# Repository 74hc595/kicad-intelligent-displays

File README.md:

# Intelligent Display Symbols/Footprints for KiCad

KiCad symbols and footprints for 4- and 8-character intelligent segmented/dot-matrix alphanumeric displays like the DL1414, DL2416, HDSP-2112, PDSP1881, etc.

At this time, the library does not include symbols/footprints for the exotic/mil-spec parts.

Some parts, like the PDSP188x and HDSP-2xxx, do not have pins in all positions. To facilitate the use of regular DIP sockets and single inline pin sockets, alternative footprints have been provided for these parts that have holes in all positions. (they end with a `_DIPxx` suffix)

(Pictures courtesy of the [Vintage Technology Association](http://www.decadecounter.com/))

## Test fixture

Included in the KiCad project is a tester board based on the atmega809 microcontroller. The `code` folder contains the firmware, and instructions are in `code/main.c`. A prebuilt hex file is also provided.

## References

[1982 Litronix Optoelectronics Catalog](https://archive.org/details/LitronixOptoelectronicsCatalog1982)

[1985 Siemens Optoelectronics Catalog](http://www.bitsavers.org/components/siemens/1985_Siemens_Optoelectronics_Catalog.pdf)

[1990 Siemens Optoelectronics Data Book](http://www.bitsavers.org/components/siemens/1990_Siemens_Optoelectronics_Data_Book.pdf)

[Broadcom Smart Alphanumeric Displays](https://www.broadcom.com/products/leds-and-displays/smart-alphanumeric-displays/parallel-interface/)

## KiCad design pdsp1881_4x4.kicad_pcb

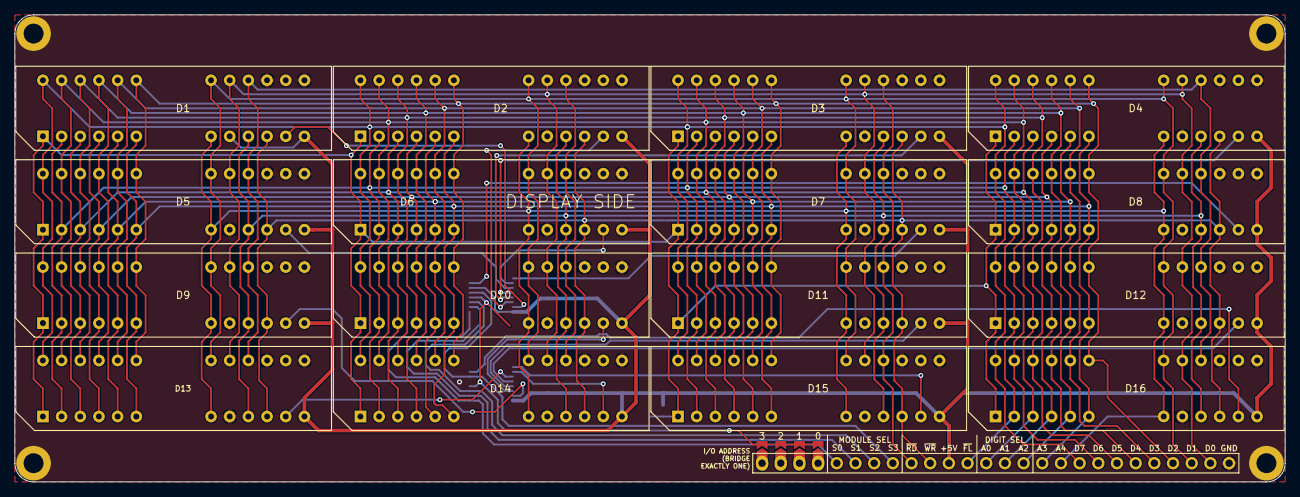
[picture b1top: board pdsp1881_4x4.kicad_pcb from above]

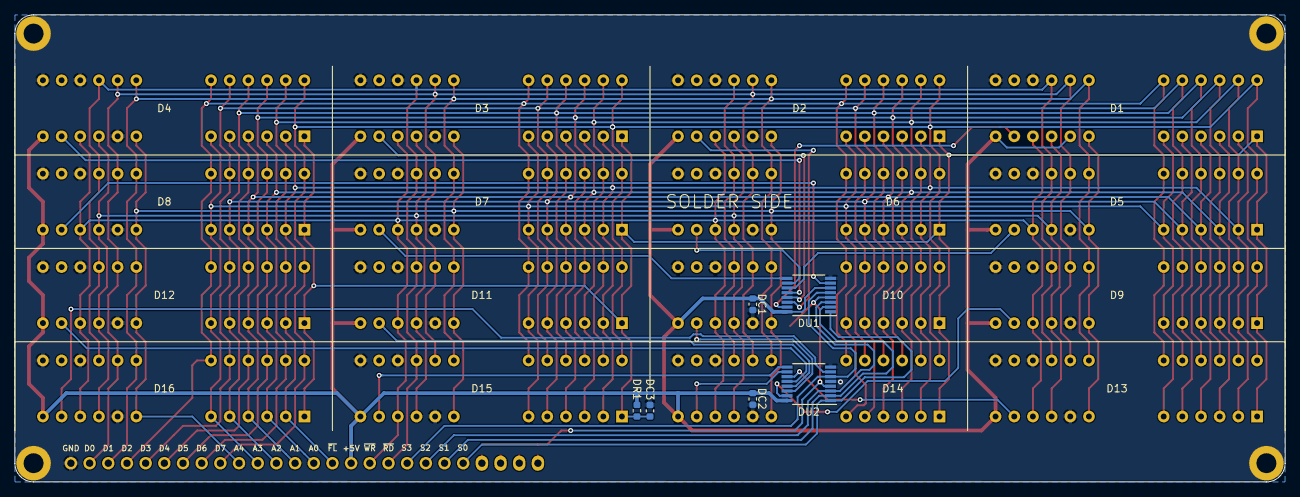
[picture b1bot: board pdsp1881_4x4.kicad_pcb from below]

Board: 2 copper layers, 172.7 x 63.5 mm, 27 parts (6 on the bottom side), 45 nets.

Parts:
D1, D2, D3, D4, D5, D6, D7, D8, D9, D10, D11, D12, D13, D14, D15, D16: PDSP1881; PDSP188x
DC1, DC2, DC3: 0.1uF; C_0603_1608Metric
DJ1: Conn_01x26; PinHeader_1x26_P2.54mm_Vertical
DJP1, DJP2, DJP3, DJP4: SolderJumper_2_Open; SolderJumper-2_P1.3mm_Open_TrianglePad1.0x1.5mm
DR1: 10k; R_0603_1608Metric
DU1, DU2: 74AHC138; TSSOP-16_4.4x5mm_P0.65mm

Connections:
/A0: D1.3, D2.3, D3.3, D4.3, D5.3, D6.3, D7.3, D8.3, D9.3, D10.3, D11.3, D12.3, D13.3, D14.3, D15.3, D16.3, DJ1.13
/A1: D1.4, D2.4, D3.4, D4.4, D5.4, D6.4, D7.4, D8.4, D9.4, D10.4, D11.4, D12.4, D13.4, D14.4, D15.4, D16.4, DJ1.14
/A2: D1.5, D2.5, D3.5, D4.5, D5.5, D6.5, D7.5, D8.5, D9.5, D10.5, D11.5, D12.5, D13.5, D14.5, D15.5, D16.5, DJ1.15
/A3: D1.6, D2.6, D3.6, D4.6, D5.6, D6.6, D7.6, D8.6, D9.6, D10.6, D11.6, D12.6, D13.6, D14.6, D15.6, D16.6, DJ1.16
/A4: D1.10, D2.10, D3.10, D4.10, D5.10, D6.10, D7.10, D8.10, D9.10, D10.10, D11.10, D12.10, D13.10, D14.10, D15.10, D16.10, DJ1.17
/D0: D1.20, D2.20, D3.20, D4.20, D5.20, D6.20, D7.20, D8.20, D9.20, D10.20, D11.20, D12.20, D13.20, D14.20, D15.20, D16.20, DJ1.25
/D1: D1.21, D2.21, D3.21, D4.21, D5.21, D6.21, D7.21, D8.21, D9.21, D10.21, D11.21, D12.21, D13.21, D14.21, D15.21, D16.21, DJ1.24
/D2: D1.25, D2.25, D3.25, D4.25, D5.25, D6.25, D7.25, D8.25, D9.25, D10.25, D11.25, D12.25, D13.25, D14.25, D15.25, D16.25, DJ1.23
/D3: D1.26, D2.26, D3.26, D4.26, D5.26, D6.26, D7.26, D8.26, D9.26, D10.26, D11.26, D12.26, D13.26, D14.26, D15.26, D16.26, DJ1.22
/D4: D1.27, D2.27, D3.27, D4.27, D5.27, D6.27, D7.27, D8.27, D9.27, D10.27, D11.27, D12.27, D13.27, D14.27, D15.27, D16.27, DJ1.21
/D5: D1.28, D2.28, D3.28, D4.28, D5.28, D6.28, D7.28, D8.28, D9.28, D10.28, D11.28, D12.28, D13.28, D14.28, D15.28, D16.28, DJ1.20
/D6: D1.29, D2.29, D3.29, D4.29, D5.29, D6.29, D7.29, D8.29, D9.29, D10.29, D11.29, D12.29, D13.29, D14.29, D15.29, D16.29, DJ1.19
/D7: D1.30, D2.30, D3.30, D4.30, D5.30, D6.30, D7.30, D8.30, D9.30, D10.30, D11.30, D12.30, D13.30, D14.30, D15.30, D16.30, DJ1.18
/DCLK: D1.12, D2.12, D3.12, D4.12, D5.12, D6.12, D7.12, D8.12, D9.12, D10.12, D11.12, D12.12, D13.12, D14.12, D15.12, D16.12
/S0: DJ1.5, DU1.1, DU2.1
/S1: DJ1.6, DU1.2, DU2.2
/S2: DJ1.7, DU1.3, DU2.3
/S3: DJ1.8, DU1.5, DU2.6
/~D1EN: D1.14, DU1.15
/~D2EN: D2.14, DU1.14
/~D3EN: D3.14, DU1.13
/~D4EN: D4.14, DU1.12
/~D5EN: D5.14, DU1.11
/~D6EN: D6.14, DU1.10
/~D7EN: D7.14, DU1.9
/~D8EN: D8.14, DU1.7
/~D9EN: D9.14, DU2.15
/~D10EN: D10.14, DU2.14
/~D11EN: D11.14, DU2.13
/~D12EN: D12.14, DU2.12
/~D13EN: D13.14, DU2.11
/~D14EN: D14.14, DU2.10
/~D15EN: D15.14, DU2.9
/~D16EN: D16.14, DU2.7
/~DISPEN: DJP1.2, DJP2.2, DJP3.2, DJP4.2, DU1.4, DU2.4
/~DRST: D1.1, D2.1, D3.1, D4.1, D5.1, D6.1, D7.1, D8.1, D9.1, D10.1, D11.1, D12.1, D13.1, D14.1, D15.1, D16.1, DC3.1, DR1.2
/~FL: D1.2, D2.2, D3.2, D4.2, D5.2, D6.2, D7.2, D8.2, D9.2, D10.2, D11.2, D12.2, D13.2, D14.2, D15.2, D16.2, DJ1.12
/~RD: D1.19, D2.19, D3.19, D4.19, D5.19, D6.19, D7.19, D8.19, D9.19, D10.19, D11.19, D12.19, D13.19, D14.19, D15.19, D16.19, DJ1.9
/~WR: D1.13, D2.13, D3.13, D4.13, D5.13, D6.13, D7.13, D8.13, D9.13, D10.13, D11.13, D12.13, D13.13, D14.13, D15.13, D16.13, DJ1.10
GND: D1.16, D1.18, D2.11, D2.16, D2.18, D3.11, D3.16, D3.18, D4.11, D4.16, D4.18, D5.11, D5.16, D5.18, D6.11, D6.16, D6.18, D7.11, D7.16, D7.18, D8.11, D8.16, D8.18, D9.11, D9.16, D9.18, D10.11, D10.16, D10.18, D11.11, D11.16, D11.18, D12.11, D12.16, D12.18, D13.11, D13.16, D13.18, D14.11, D14.16, D14.18, D15.11, D15.16, D15.18, D16.11, D16.16, D16.18, DC1.2, DC2.2, DC3.2, DJ1.26, DU1.8, DU2.5, DU2.8
unnamed: DJ1.1, DJP1.1
unnamed: DJ1.2, DJP2.1
unnamed: DJ1.3, DJP3.1
unnamed: DJ1.4, DJP4.1
VCC: D1.11, D1.15, D2.15, D3.15, D4.15, D5.15, D6.15, D7.15, D8.15, D9.15, D10.15, D11.15, D12.15, D13.15, D14.15, D15.15, D16.15, DC1.1, DC2.1, DJ1.11, DR1.1, DU1.6, DU1.16, DU2.16

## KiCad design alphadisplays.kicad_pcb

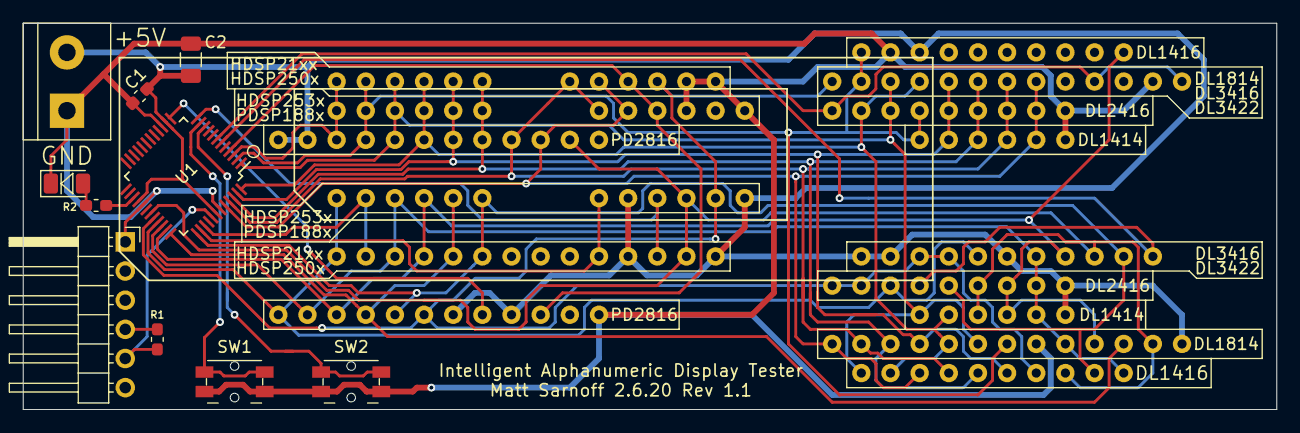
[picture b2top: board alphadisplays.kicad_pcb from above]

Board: 2 copper layers, 109.2 x 33.7 mm, 18 parts (0 on the bottom side), 30 nets.

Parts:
C1: 0.1uF; C_0603_1608Metric_Pad1.05x0.95mm_HandSolder
C2: 10uF; C_1206_3216Metric
D1: DL1414
D2: DL1416
D3: DL2416
D4: DL3416; DL34xx
D5: DL1814
D6: HDSP-250x
D7: PDSP188x
D8: PD2816
D9: 1206 LED; LED_1206_3216Metric
J1: FTDI 5V; PinHeader_1x06_P2.54mm_Horizontal
J2: Screw_Terminal_01x02; TerminalBlock_bornier-2_P5.08mm
R1: 4.7k; R_0603_1608Metric_Pad1.05x0.95mm_HandSolder
R2: 1k; R_0603_1608Metric_Pad1.05x0.95mm_HandSolder
SW1, SW2: SW_SPST; Panasonic_EVQPUL_EVQPUC
U1: ATmega809-A; TQFP-48_7x7mm_P0.5mm

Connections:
/A0: D1.5, D2.10, D3.8, D4.7, D5.9, D6.3, D7.3, D8.2, U1.34
/A1: D1.4, D2.11, D3.7, D4.8, D5.10, D6.4, D7.4, D8.3, U1.35
/A2: D5.11, D6.5, D7.5, D8.4, U1.36
/A3: D2.9, D3.5, D4.10, D6.6, D7.6, D8.5, U1.37
/A4: D6.10, D7.10, U1.38
/CUE: D3.4, D4.11, U1.6
/D0: D1.8, D2.3, D3.11, D4.16, D5.1, D6.19, D7.20, D8.15, U1.44
/D1: D1.9, D2.4, D3.12, D4.17, D5.2, D6.20, D7.21, D8.16, U1.45
/D2: D1.10, D2.5, D3.13, D4.18, D5.3, D6.23, D7.25, D8.17, U1.46
/D3: D1.11, D2.6, D3.14, D4.19, D5.4, D6.24, D7.26, D8.18, U1.47
/D4: D1.2, D2.2, D3.17, D4.20, D5.5, D6.25, D7.27, D8.19, U1.48
/D5: D1.1, D2.1, D3.16, D4.21, D5.6, D6.26, D7.28, D8.20, U1.1
/D6: D1.12, D2.20, D3.15, D4.22, D5.7, D6.27, D7.29, D8.21, U1.2
/D7: D6.28, D7.30, D8.22, U1.3
/HDSPCLK: D6.12, D7.12, U1.12
/PD2816CLK: D8.8, U1.13
/UPDI: J1.5, R1.2, U1.41
/~BL: D3.18, D4.14, D5.14, U1.7
/~CE: D2.7, D3.1, D3.2, D4.3, D4.4, D5.26, D6.17, D7.14, D8.6, U1.32
/~CLR: D3.3, D4.5, D6.1, D7.1, D8.1, U1.33
/~FL: D6.2, D7.2, U1.39
/~RD: D6.18, D7.19, D8.10, U1.4
/~SW1: SW1.2, U1.11
/~SW2: SW2.2, U1.10
/~WR: D1.3, D2.8, D3.6, D4.9, D5.12, D6.13, D7.13, D8.14, U1.31
GND: C1.2, C2.2, D1.7, D2.19, D3.10, D4.12, D5.8, D6.15, D6.16, D7.16, D7.18, D8.12, D9.1, J1.1, J2.2, SW1.1, SW2.1, U1.15, U1.29, U1.43
unnamed: D9.2, R2.1
unnamed: J1.4, R1.1
unnamed: R2.2, U1.27
VCC: C1.1, C2.1, D1.6, D2.18, D3.9, D4.1, D4.2, D4.6, D5.13, D6.11, D6.14, D7.11, D7.15, D8.7, D8.9, D8.23, D8.24, J2.1, U1.14, U1.28, U1.42

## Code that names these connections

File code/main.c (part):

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/* ~CE - chip enable (active low) */
#define nCE_PORT        E
#define nCE_PIN         2
/* ~CLR (2416/3416/3422) / ~RST (HDSP-2xxx/PD2816) - clear/reset display (active low) */
#define nCLR_PORT       E
#define nCLR_PIN        3
/* ~RD (HDSP-2xxx/PD2816) - read (active low) */
#define nRD_PORT        B
#define nRD_PIN         0
/* CUE (2416/3416/3422) - cursor enable (active high) */
#define CUE_PORT        B
#define CUE_PIN         2
/* ~BL (2416/3416/3422) - blank display (active low) */
#define nBL_PORT        B
#define nBL_PIN         3
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#define nSW2_PORT       C
#define nSW2_PIN        0
/* HDSP-2xxx clock detect */
#define HDSPCLK_PORT    C
#define HDSPCLK_PIN     2
/* PD2816 clock detect */
#define PD2816CLK_PORT  C
#define PD2816CLK_PIN   3
/* Data lines D0-D7 */
#define DATA_PORT       A
/* Address lines A0-A4 and ~FL. ~CU is A3. */
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  /* clear cursor from all positions */
  setCursorMask(0);
  /* cursor on */
  pin_high(CUE);
  displayString_P(msg_abcdefgh);
  waitMillis(delay);
  /* show cursor individually in all digits */
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  waitMillis(delay);
  /* cursor off */
  setCursorMask(0);
  pin_low(CUE);
}


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  pin_output_high(nWR);
  pin_output_high(nCE);
  pin_output_high(nRD);
  pin_output_low(CUE);
  pin_output_low(nBL);
  pin_output_high(LED);
  port_outputs(DATA);
  port_outputs(ADDRESS);
  pin_input_pullup(nSW1);
  pin_input_pullup(nSW2);
  pin_input_pullup(HDSPCLK);
  pin_input_pullup(PD2816CLK);
  hardResetDisplay();

  /* if SW2 is held down on powerup, toggle the swap-A1/A0 bit */
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  while (--count) {
    /* It should not be physically possible to have a PD2816 and HDSP2xxx */
    /* inserted at the same time */
    if (pin_is_low(HDSPCLK)) {
      setDisplayType(HDSP2xxx);
      displayString_P(msg_hdsp2xxx);
      waitForButton2Press();
      goto run;
    } else if (pin_is_low(PD2816CLK)) {
      setDisplayType(PD2816);
      displayString_P(msg_pd2816);
      waitForButton2Press();
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
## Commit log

2020-01-04 initial commit
    I haven't tested these yet!! Just wanted to get them online
2020-01-04 remove ? from refdes
2020-01-04 add footprint assoc. to DL1814
2020-01-05 remove incorrect 3d model specifications
2020-01-05 wip: laying out test board
2020-01-07 fix courtyard
2020-01-07 add HDSP-253x aliases
2020-01-07 tester board ready for fab
2020-01-07 add png pinout diagrams
2020-01-07 add datasheet links
2020-01-12 swap A0/A1 on 3416/3422
2020-01-12 update board rev number
2020-01-22 more board tweaks
2020-01-22 schematic info
2020-01-22 add gitignore
2020-01-22 workin' on code
2020-01-24 workin on code
2020-02-03 test cursor and blanking
2020-02-04 lots more tests
2020-02-04 test user defined characters
2020-02-04 add some more delays, probably not needed
    identified two PD2816s in my inventory that seem to have RAM issues,
    with bit 4 sometimes getting stuck at 0. One has an 8540 date code,
    another is 8708.
    Out of the 17 PD2816s I have, 14 passed all tests, 2 failed the RAM read
    test and had wrong characters during the blink/underline test, and 1
    flickers visibly (dying internal oscillator?) but otherwise works fine.
2020-02-05 menu, and other tweaks
2020-02-05 add user-defined chars to ascii range
2020-02-05 clear display before starting menu
2020-02-05 store menu selections in eeprom
2020-02-05 hold SW2 on startup to swap A0/A1
    won't be necessary with rev1.1 boards
    i think this is done for now
2020-02-07 board tweaks, docs
2020-02-08 fix drc errors
    (except overlapping courtyards, which are fine)
2020-05-30 add 4x4 PDSP1881 (32x4 character) display board
